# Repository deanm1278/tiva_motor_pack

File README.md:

# tiva_motor_pack
3 axis (2 servo 1 stepper) motor booster pack for EK-TM4C123GXL launchpad board

This booster pack drives 2 servos with encoders and 1 stepper motor.

The resolution limits are not yet well tested, but it definitely runs 2 brushed dc servos at 10khz velocity sampling and 1 stepper at 1/256 microstepping very smoothly. Stepper tested is a NEMA 17 2.0A at 2.8V motor that runs very smooth when microstepped. Servos tested are Harmonic drive RH-8 motors with Tamagawa encoders and also run well.

The software libraries include PID contol for the servos. Further tuning of PID may be necessary.

Servo drivers are TI DRV8871 (datasheet here: http://www.ti.com/lit/ds/symlink/drv8871.pdf)
stepper driver is a TI DRV8881E (datasheet here: http://www.ti.com/lit/ds/symlink/drv8881.pdf)

Autotune feature on the DRV8881E seems to work quite nicely :)

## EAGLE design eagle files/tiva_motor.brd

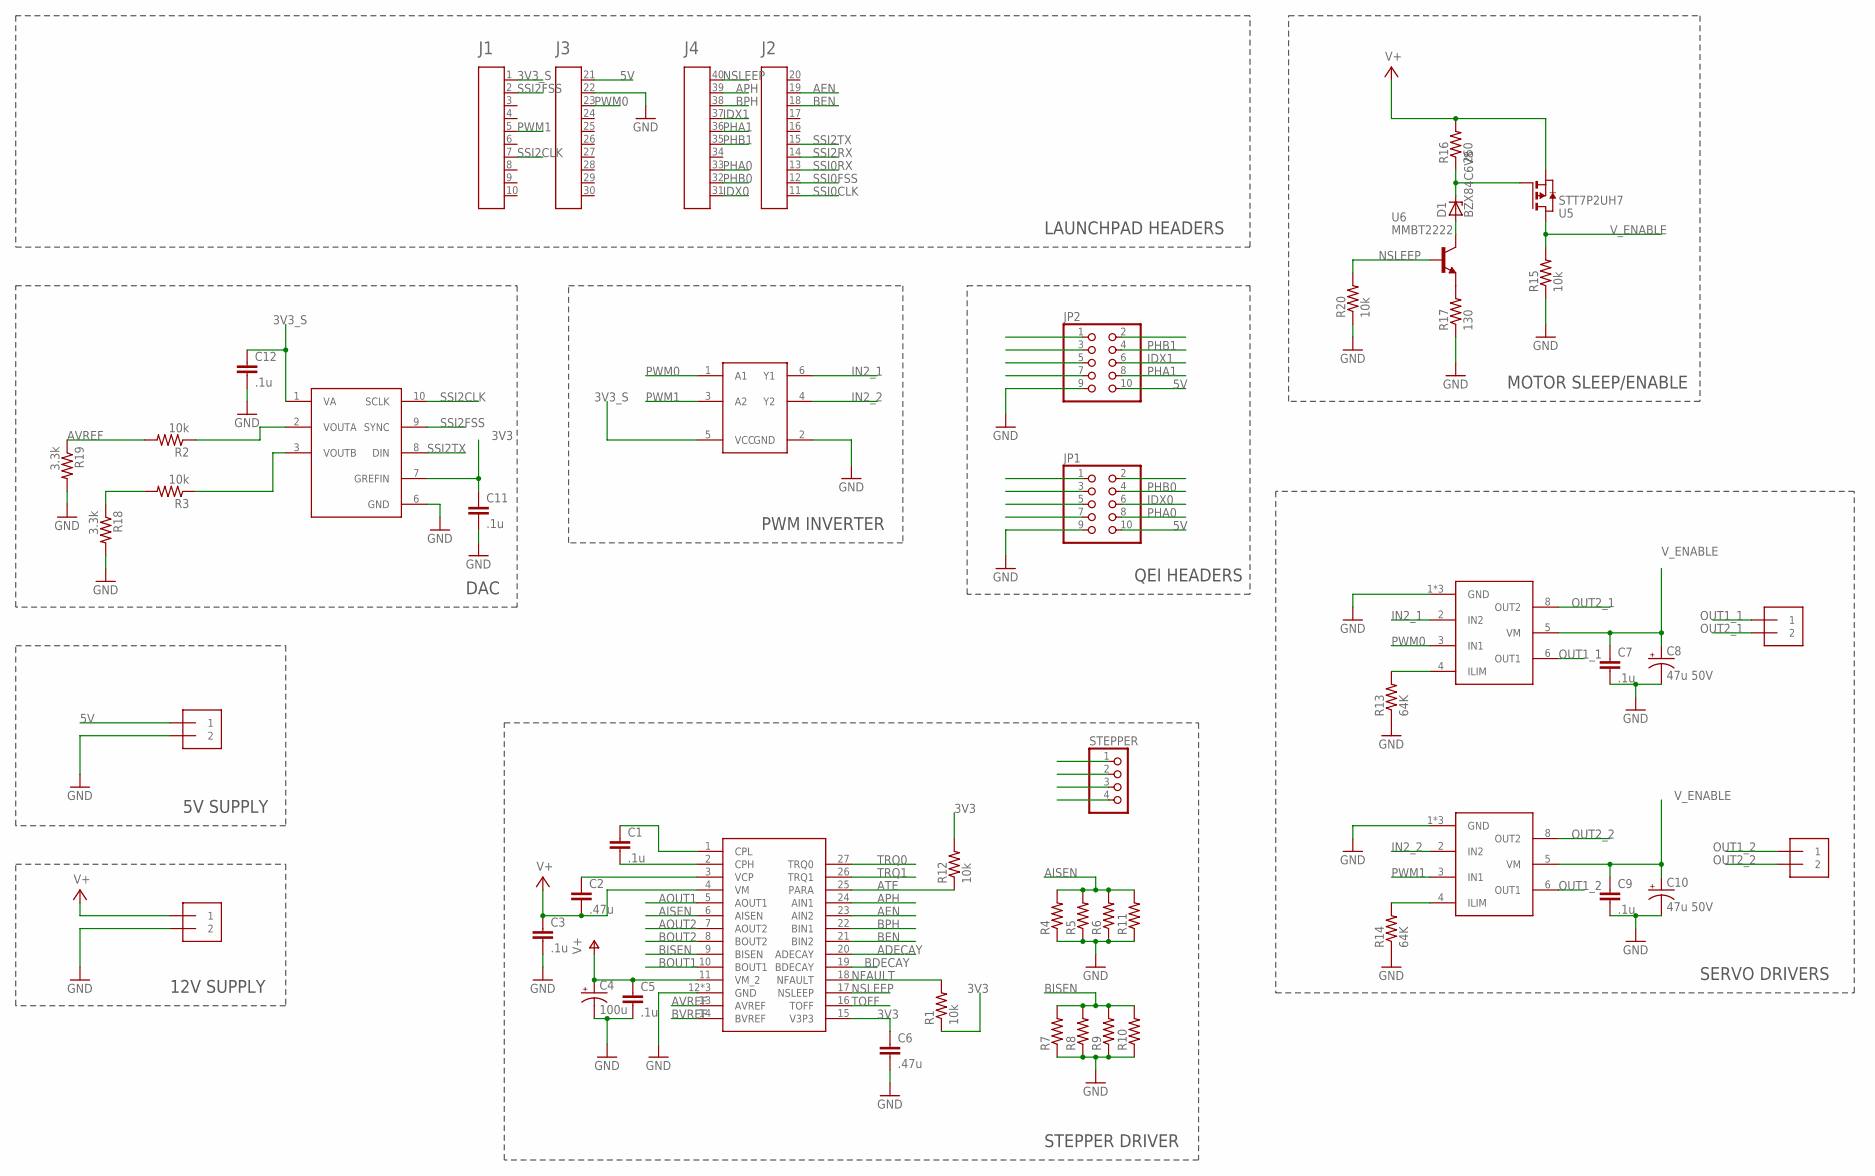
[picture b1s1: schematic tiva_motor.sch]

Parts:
5V, 12V: 1X2-3.5MM
A1: HEADER4X10-BOOSTERPACK; 4X10-BOOSTERPACK
C1, C3, C5, C7, C9: .1u; C0603
C2, C6: .47u; C0603
C4: 100u; 153CLV-0605
C8, C10: 47u 50V; 153CLV-0605
C11, C12: .1u; C0402
D1: BZX84C6V8; SOT-23
JP1, JP2: PINHD-2X5; 2X05
M1, M2: 1X2-3.5MM
R1, R12, R15, R20: 10k; R0402
R2, R3: 10k; R0603
R4, R5, R6, R7, R8, R9, R10, R11: R-US_R0603; R0603
R13, R14: 64K; R0603
R16: 260; R0805
R17: 130; R1206
R18, R19: 3.3k; R0603
STEPPER: PINHD-1X4; 1X04
U1: DRV8881; TSSOP28
U2, U4: DRV8871; SOIC127P600X170-9N
U5: STT7P2UH7; SOT23-6
U6: MMBT2222; SOT-23
U8: DAC082S085; SOP50P490X110-10N
U9: NC7WZ14; SC70-6

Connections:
3V3: C6.1, C11.1, R1.1, R12.2, U1.15 (V3P3), U8.7 (GREFIN)
3V3_S: A1.1, C12.1, U8.1 (VA), U9.5 (VCC)
5V: 5V.1, A1.21, JP1.10, JP2.10
ADECAY: U1.20 (ADECAY)
AEN: A1.19, U1.23 (AIN2)
AISEN: R4.2, R5.2, R6.2, R11.2, U1.6 (AISEN)
AOUT1: STEPPER.1, U1.5 (AOUT1)
AOUT2: STEPPER.2, U1.7 (AOUT2)
APH: A1.39, U1.24 (AIN1)
ATE: R12.1, U1.25 (PARA)
AVREF: R2.2, R19.1, U1.13 (AVREF)
BDECAY: U1.19 (BDECAY)
BEN: A1.18, U1.21 (BIN2)
BISEN: R7.2, R8.2, R9.2, R10.2, U1.9 (BISEN)
BOUT1: STEPPER.3, U1.10 (BOUT1)
BOUT2: STEPPER.4, U1.8 (BOUT2)
BPH: A1.38, U1.22 (BIN1)
BVREF: R3.2, R18.1, U1.14 (BVREF)
GND: 5V.2, 12V.2, A1.22, C3.2, C4.-, C5.2, C6.2, C7.2, C8.-, C9.2, C10.-, C11.2, C12.2, JP1.9, JP2.9, R4.1, R5.1, R6.1, R7.1, R8.1, R9.1, R10.1, R11.1, R13.1, R14.1, R15.1, R17.1, R18.2, R19.2, R20.1, U1.12 (GND), U1.28 (GND), U1.P$1 (GND), U2.1 (GND), U2.7 (GND), U2.9 (GND), U4.1 (GND), U4.7 (GND), U4.9 (GND), U8.6 (GND), U9.2 (GND)
IDX0: A1.31, JP1.6
IDX1: A1.37, JP2.6
ILIM: R13.2, U2.4 (ILIM)
ILIM1: R14.2, U4.4 (ILIM)
IN2_1: U2.2 (IN2), U9.6 (Y1)
IN2_2: U4.2 (IN2), U9.4 (Y2)
unnamed: C1.2, U1.2 (CPH)
unnamed: C1.1, U1.1 (CPL)
unnamed: C2.1, U1.3 (VCP)
unnamed: R17.2, U6.2 (E)
unnamed: D1.3 (C), R16.1, U5.3 (G)
unnamed: R2.1, U8.2 (VOUTA)
unnamed: R3.1, U8.3 (VOUTB)
unnamed: D1.1 (A), U6.3 (C)
NC: JP1.2
NFAULT: R1.2, U1.18 (NFAULT)
NSLEEP: A1.40, R20.2, U1.17 (NSLEEP), U6.1 (B)
OUT1_1: M1.1, U2.6 (OUT1)
OUT1_2: M2.1, U4.6 (OUT1)
OUT2_1: M1.2, U2.8 (OUT2)
OUT2_2: M2.2, U4.8 (OUT2)
PHA0: A1.33, JP1.8
PHA1: A1.36, JP2.8
PHB0: A1.32, JP1.4
PHB1: A1.35, JP2.4
PWM0: A1.23, U2.3 (IN1), U9.1 (A1)
PWM1: A1.5, U4.3 (IN1), U9.3 (A2)
SSI0CLK: A1.11
SSI0FSS: A1.12
SSI0RX: A1.13
SSI2CLK: A1.7, U8.10 (SCLK)
SSI2FSS: A1.2, U8.9 (SYNC)
SSI2RX: A1.14
SSI2TX: A1.15, U8.8 (DIN)
TOFF: U1.16 (TOFF)
TRQ0: U1.27 (TRQ0)
TRQ1: U1.26 (TRQ1)
V+: 12V.1, C2.2, C3.1, C4.+, C5.1, R16.2, U1.4 (VM), U1.11 (VM_2), U5.4 (S)
V_ENABLE: C7.1, C8.+, C9.1, C10.+, R15.2, U2.5 (VM), U4.5 (VM), U5.1 (D), U5.2 (D), U5.5 (D), U5.6 (D)

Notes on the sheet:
LAUNCHPAD HEADERS
DAC
5V SUPPLY
12V SUPPLY
PWM INVERTER
QEI HEADERS
MOTOR SLEEP/ENABLE
SERVO DRIVERS
STEPPER DRIVER

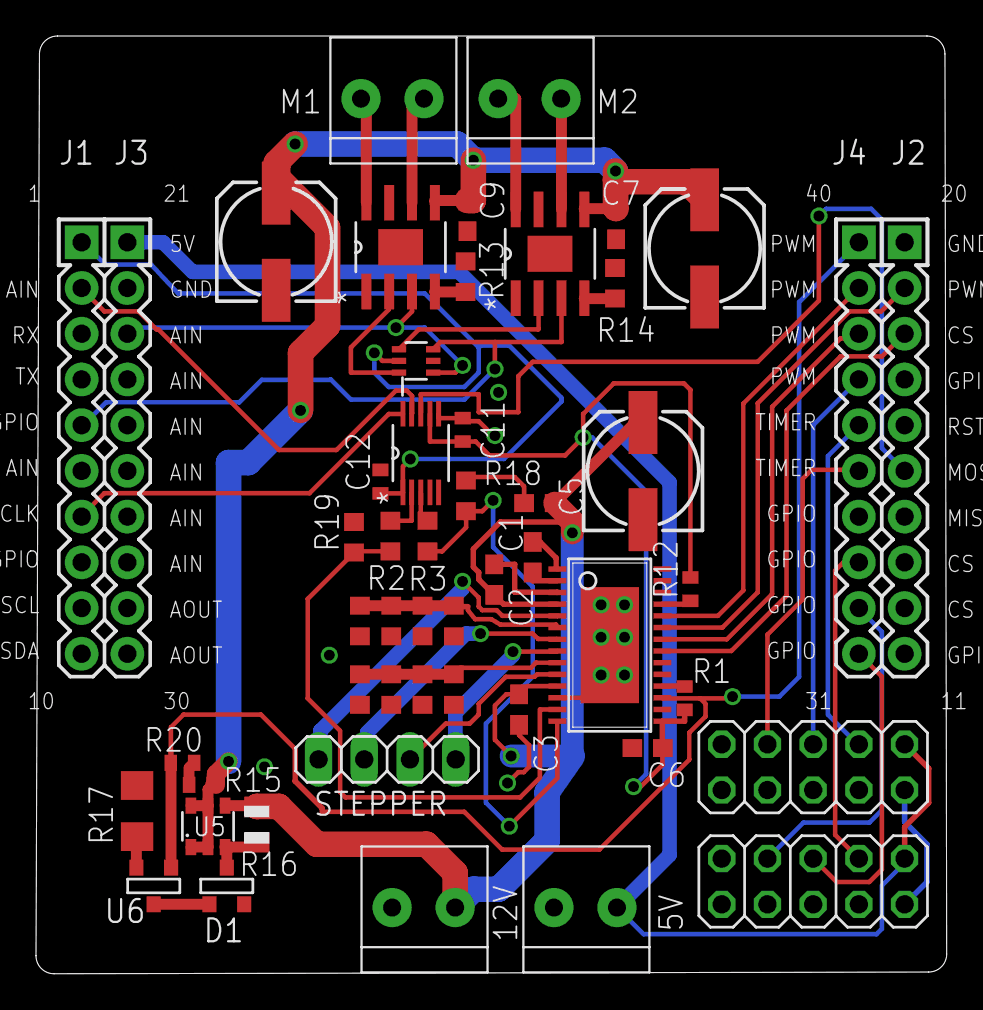
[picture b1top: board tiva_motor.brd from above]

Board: 2 copper layers, 50.6 x 52.1 mm, 48 parts (0 on the bottom side), 48 nets.

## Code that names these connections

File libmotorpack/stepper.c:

/*
 * stepper.c
 *
 *  Created on: May 1, 2016
 *      Author: Dean Miller
 */

#include <stdint.h>
#include <stdbool.h>

#include "inc/hw_ints.h"
#include "inc/hw_memmap.h"

#include "driverlib/pin_map.h"
#include "driverlib/gpio.h"
#include "driverlib/sysctl.h"
#include "driverlib/timer.h"
#include "driverlib/interrupt.h"

#include "stepper.h"
#include "DAC082S085.h"

extern void TIMER2IntHandler(void);

void stepper_init(struct stepper *s){
	DAC082S085_init(&s->dac, SSI2_BASE);
	s->stepping_rate = 0;
	s->div = 1;

	// Enable the timer
	//
	SysCtlPeripheralEnable(SYSCTL_PERIPH_TIMER2);
	TimerConfigure(TIMER2_BASE, TIMER_CFG_PERIODIC);

	IntEnable(INT_TIMER2A);
	TimerIntRegister(TIMER2_BASE, TIMER_A, TIMER2IntHandler);
	TimerIntEnable(TIMER2_BASE, TIMER_TIMA_TIMEOUT);

	//set up other necessary GPIO
	SysCtlPeripheralEnable(SYSCTL_PERIPH_GPIOB);
	GPIOPinTypeGPIOOutput(GPIO_PORTB_BASE, GPIO_PIN_2 | GPIO_PIN_3); //AEN, BPH

	SysCtlPeripheralEnable(SYSCTL_PERIPH_GPIOE);
	GPIOPinTypeGPIOOutput(GPIO_PORTE_BASE, GPIO_PIN_0); //BEN

	SysCtlPeripheralEnable(SYSCTL_PERIPH_GPIOF);
	GPIOPinTypeGPIOOutput(GPIO_PORTF_BASE, GPIO_PIN_3); //APH
}

void stepper_stop(struct stepper *s){
	TimerDisable(TIMER2_BASE, TIMER_A);
	GPIOPinWrite(GPIO_PORTB_BASE, GPIO_PIN_2, 0);
	GPIOPinWrite(GPIO_PORTE_BASE, GPIO_PIN_0, 0);
	s->t_val = 0;
}

void stepper_start(struct stepper *s){
	s->fires_this_move = 0;
	//
	// Enable the timer.
	//
	TimerEnable(TIMER2_BASE, TIMER_A);
	GPIOPinWrite(GPIO_PORTB_BASE, GPIO_PIN_2, GPIO_PIN_2);
	GPIOPinWrite(GPIO_PORTE_BASE, GPIO_PIN_0, GPIO_PIN_0);
}

void stepper_set_stepping_rate(struct stepper *s, uint32_t stepping_rate){
	s->stepping_rate = stepping_rate;
	TimerLoadSet(TIMER2_BASE, TIMER_A, SysCtlClockGet()/(s->stepping_rate * (256 / s->div)));
}

void stepper_move_steps(struct stepper *s, uint32_t steps){
	stepper_start(s);
	while(s->fires_this_move < steps);
	stepper_stop(s);
}

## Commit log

2016-05-02 added board pic
